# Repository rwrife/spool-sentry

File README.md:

# Spool Sentry

> USB-powered ESP32-C3 monitor for 3D-printing hobbyists to track dry-box humidity, temperature, and filament spool mass through a private local dashboard without controlling heaters or printers.

## Overview

Spool Sentry is a small, repairable monitor for a passive filament dry box. A load cell under one spool records mass trends while a digital temperature/humidity sensor records the box environment. An ESP32-C3-class controller keeps bounded local history and serves a phone/desktop-friendly web interface on the local network. USB CDC remains the setup and recovery path.

The goal is practical awareness: see whether a box is staying dry, record desiccant changes, and estimate remaining filament after the user enters empty-spool mass. It is **not** a dryer controller, printer integration, certified hygrometer, or safety device.

## Motivation

Opaque boxes hide both environmental drift and dwindling material. Stick-on hygrometers show only the present, and manually weighing a spool interrupts storage. Spool Sentry combines two explainable observations without requiring a vendor account, subscription, or internet service.

## Target users

- Home 3D-printing hobbyists who store moisture-sensitive filament
- Small workshops that want a local history for one frequently used spool
- Makers who prefer editable hardware, replaceable sensors, and portable data

## Concrete use cases

- Check current box humidity and temperature from a phone on the same LAN.
- View hourly trends and annotate a desiccant recharge or spool swap.
- Tare/calibrate the scale, enter an empty-spool mass, and see gross/net mass with an uncertainty indicator.
- Export measurements and events as CSV/JSON before clearing local history.
- Recover configuration over USB if Wi-Fi credentials change.

## Intended workflow

1. Assemble the low-voltage carrier, sensor lead, load-cell platform, and enclosure using the bring-up guide that the backlog will create.
2. Power it from a suitable USB 5 V supply; no battery or mains wiring is part of the project.
3. Hold the physical setup button to open a short-lived onboarding session, then configure local Wi-Fi from the device-hosted page or USB CDC.
4. Calibrate with a documented reference mass, enter the spool's empty mass, and place the spool on the platform.
5. Review live values and local trends, add spool/desiccant events, and export or delete data at any time.

## MVP features

- One replaceable load-cell/ADC channel and one digital humidity/temperature channel
- Explicit sensor freshness, calibration state, and invalid/out-of-range statuses
- Gross mass, user-derived net filament estimate, and visible uncertainty—not false precision
- Bounded flash history with retention controls and event annotations
- Responsive local web UI with keyboard, screen-reader, reduced-motion, high-contrast, and non-color-only states
- Versioned CSV/JSON export and JSON backup/restore
- USB CDC provisioning, diagnostics, firmware recovery, and Wi-Fi-free snapshot access
- Physical setup/tare button and status indicator

## Non-goals

- Heater, fan, mains, battery-charging, relay, or printer control
- Fire, smoke, flood, food, medical, or life-safety monitoring
- Certified environmental measurement or guaranteed filament condition/print quality
- Automatic material-type diagnosis, purchasing, cloud accounts, remote internet access, or multi-site fleet management
- Multi-spool inventory, RFID, camera, or slicing software integration in the MVP

## Privacy, permissions, and data storage

Spool Sentry has no cloud backend, telemetry, advertising, or required account. Measurements, calibration data, annotations, and network configuration remain on the device; exports are created only when requested. The local web app requests no phone contacts, location, camera, microphone, Bluetooth, or notification permission. Wi-Fi access is limited to local setup and local device use. USB works without network access.

The baseline LAN protocol is not a promise of hostile-network security: deployment assumes a trusted home/workshop LAN, uses proof-of-presence onboarding, rejects cross-origin mutation, and keeps remote access disabled. Documentation will explain credential reset, export redaction, retention, deletion, and the limitations of unencrypted local HTTP if that remains the chosen transport.

## Safety limits

- SELV USB 5 V input only; use a suitable enclosed/certified USB supply.
- No connection to printer power, heaters, mains, batteries, or safety interlocks.
- Keep electronics away from hot zones, moving printer parts, liquids, and loose filament paths.
- Load readings are informational. Do not use the platform to support people, hazardous loads, or critical processes.
- Humidity/temperature readings and remaining-filament estimates can drift or fail. The device must surface stale/invalid data rather than imply safety or guaranteed print success.

## Hardware and source-of-truth plan

The planned editable KiCad project is:

- `hardware/spool-sentry.kicad_pro`
- `hardware/spool-sentry.kicad_sch`
- `hardware/spool-sentry.kicad_pcb`

These files **do not exist yet**; this repository is currently a documentation/backlog scaffold. The backlog requires real editable KiCad sources, ERC/DRC evidence, firmware/app builds, bring-up measurements, and fabrication outputs before any hardware-complete claim.

Final BOM data belongs in KiCad schematic symbol properties (`Manufacturer`, `MPN`, supplier fields, and notes) and is exported to tracked `bom/bom.csv`. `bom/preliminary-bom.csv` is planning-only and contains no validated sourcing or prices.

## Current status and milestones

**Status: requirements/architecture baseline plus toolchain proof.** The v0.1 requirements, editable architecture diagrams, protocol schema/fixture, risk register, and verification matrix are frozen. A pinned Rust host-test and ESP32-C3 target-link proof exists, but there is still no schematic, PCB, functional firmware/app, calibrated instrument, fabricated board, assembly, ERC/DRC result, flash/boot evidence, or bench/field test.

1. Freeze measurable requirements and risk boundaries.
2. Select exact components from manufacturer datasheets and create the KiCad schematic/BOM.
3. Lay out and verify the carrier PCB.
4. Build firmware and the local web companion against simulated interfaces.
5. Assemble, calibrate, integrate, and publish honest fabrication/release evidence.

See [PLAN.md](PLAN.md), the canonical [v0.1 requirements](docs/requirements.md), [architecture](docs/architecture.md), [risk register](docs/risk-register.md), [verification matrix](docs/verification-matrix.md), and the GitHub issue backlog.

## Development quickstart

The currently implemented checks require Python 3 plus rustup. The proof pins and installs its exact Rust version, components, and ESP32-C3 target:

```sh
./scripts/verify.sh
```

This checks requirement traceability, local Markdown links, the protocol schema/fixture, Rust formatting/clippy/host tests, and an ESP32-C3 release link. See [the toolchain decision](docs/toolchain.md) for exact evidence limits. KiCad 9+, the companion Node/pnpm workspace, selected-part drivers, flashing, and bench procedures arrive in later issues and must not be presented as working yet.

## License

Initial documentation is available under the MIT License. A mature release will add explicit hardware/firmware/software license files and third-party notices before publishing fabrication outputs.

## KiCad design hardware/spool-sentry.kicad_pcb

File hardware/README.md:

# Hardware design artifacts

This directory now carries the schematic source-of-truth for the Spool Sentry carrier board.

## Included files

- `spool-sentry.kicad_pro` / `spool-sentry.kicad_sch`: KiCad 9 project + schematic
- `sym-lib-table`, `fp-lib-table`: local library bindings used by this schematic
- `lib/spool-sentry.kicad_sym`: project-local custom symbols (XIAO ESP32-C3 module, NAU7802 ADC)
- `lib/spool-sentry.pretty/XIAO_ESP32C3.kicad_mod`: project-local XIAO module footprint
- `lib/spool-sentry.dcm`: symbol documentation metadata

## What this schematic covers

- USB 5V SELV power entry and protection path (USB-C UFP + PPTC + TVS + reverse-current block)
- Controller module (`U1`: Seeed XIAO ESP32-C3)
- Bridge ADC path (`U2`: NAU7802) and load-cell connector (`J2`)
- Environmental sensor path (`U3`: SHT40) on shared I2C
- Dedicated user button (`SW1`) for tare/calibration/recovery interactions
- Status RGB indicator (`D3` + current-limit resistors)
- Test points for safe bring-up/diagnostics

## Regenerating verification artifacts

From the repository root:

```bash
# Schematic ERC (text report)
kicad-cli sch erc --format report \
  --output docs/verification/kicad-erc.rpt \
  hardware/spool-sentry.kicad_sch

# Netlist + BOM exports from schematic symbol properties
./scripts/export_schematic_bom.py hardware/spool-sentry.kicad_sch

# Optional external schematic analyzer outputs (JSON + text)
# (path depends on local Hermes skill checkout)
# python3 <path-to-analyze_schematic.py> hardware/spool-sentry.kicad_sch --output docs/verification/schematic-analysis.json
# python3 <path-to-analyze_schematic.py> hardware/spool-sentry.kicad_sch --output docs/verification/schematic-analysis.txt --text
```

The issue-specific validation summary is in
`docs/verification/issue-2-hardware-schematic.md`.

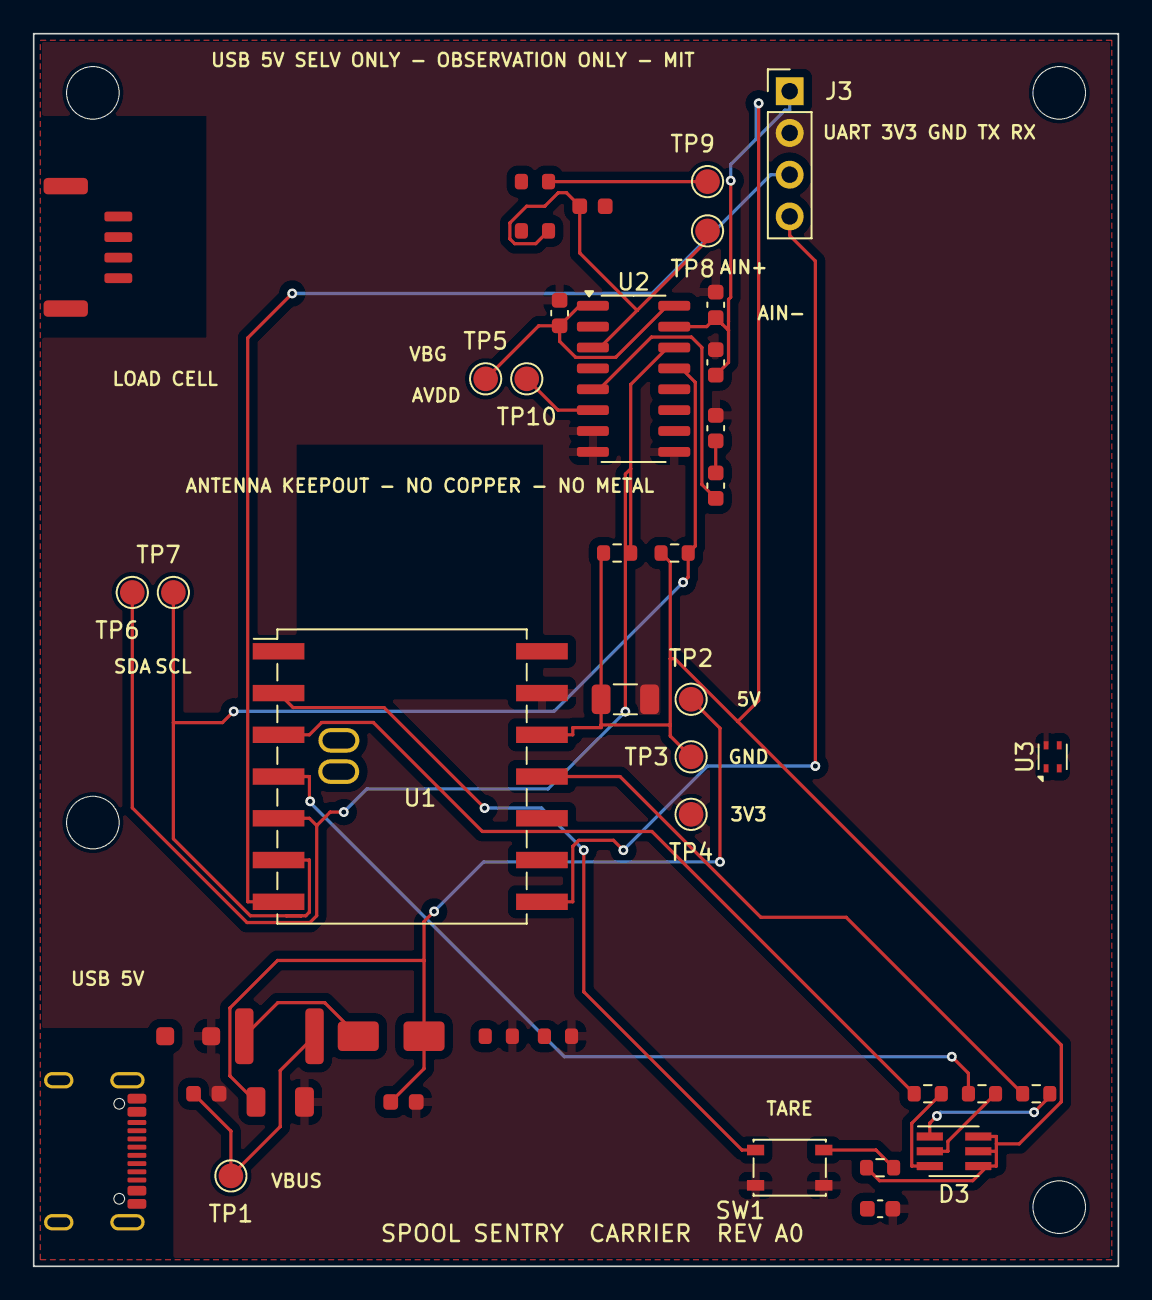
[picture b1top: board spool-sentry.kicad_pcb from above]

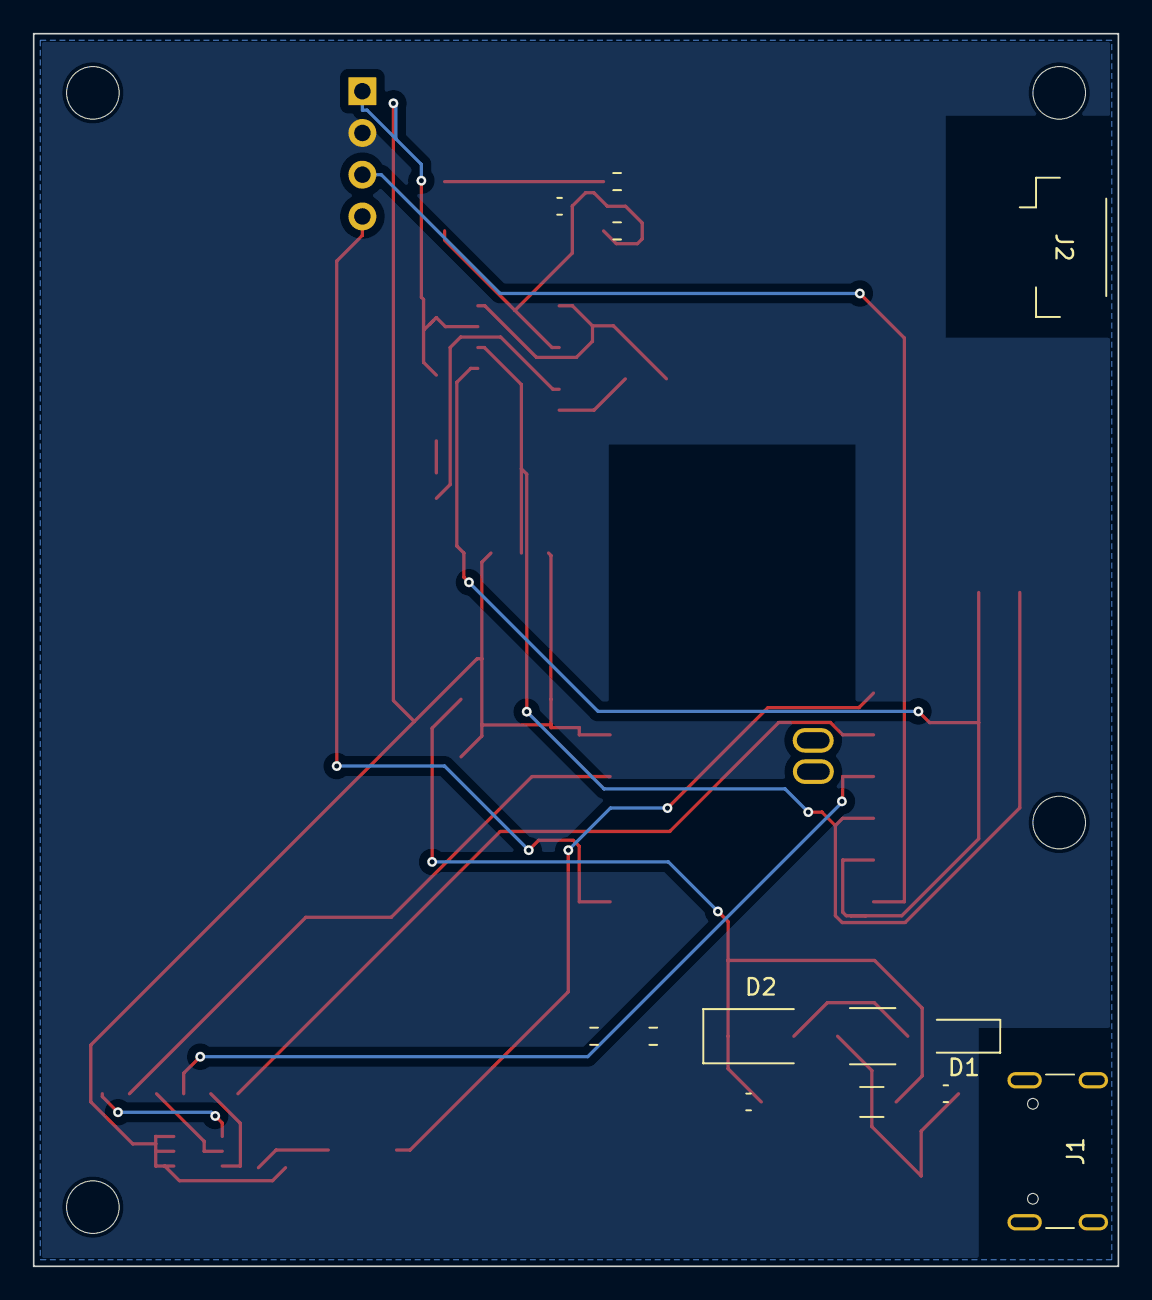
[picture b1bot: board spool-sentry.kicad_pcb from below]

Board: 2 copper layers, 66.0 x 75.0 mm, 46 parts (13 on the bottom side), 25 nets.

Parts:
C1, C3: C_1206_3216Metric
C2, C4, C5, C6, C7, C8, C9, C10, C11: C_0603_1608Metric
D1: D_SOD-123F
D2: D_SMA
D3: LED_Avago_PLCC6_3x2.8mm
F1: Fuse_1812_4532Metric
J1: USB_C_Receptacle_GCT_USB4105-xx-A_16P_TopMnt_Hori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; USB_C_Receptacle_GCT_USB4105-xx-A_16P_TopMnt_Horizontal
J2: JST_GH_SM04B-GHS-TB_1x04-1MP_P1.25mm_Horizontal
J3: PinHeader_1x04_P2.54mm_Vertical
MH1, MH2, MH3, MH4: MountingHole_3.2mm_M3
R1, R2, R3, R4, R5, R6, R7, R8, R9, R10: R_0603_1608Metric
SW1: SW_SPST_PTS810
TP1, TP2, TP3, TP4, TP5, TP6, TP7, TP8, TP9, TP10: TestPoint_Pad_D1.5mm
U1: Seeed XIAO ESP32-C3; XIAO_ESP32C3
U2: SOIC-16_3.9x9.9mm_P1.27mm
U3: Sensirion_DFN-4_1.5x1.5mm_P0.8mm_SHT4x_NoCentralP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; Sensirion_DFN-4_1.5x1.5mm_P0.8mm_SHT4x_NoCentralPad

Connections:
+3V3: C3.1, C4.1, C5.1, D3.4, D3.5, D3.6, J3.1, R5.1, R6.1, R7.1, TP3.1, U1.12, U2.15, U3.3
+5V_XIAO: C1.1, C2.1, D2.1, TP2.1, U1.14
AIN+: C8.1, R3.2, TP8.1, U2.3
AIN-: C8.2, R4.2, TP9.1, U2.2
AVDD_3V0: C6.1, J2.1, TP5.1, U2.1, U2.16
BUTTON_N: C10.1, R7.2, SW1.1, U1.2
CC1: J1.A5, R1.1
CC2: J1.B5, R2.1
GND: C1.2, C2.2, C3.2, C4.2, C5.2, C6.2, C7.2, C10.2, C11.2, D1.2, J1.A1, J1.A12, J1.B1, J1.B12, J1.S1, J2.2, J2.MP, J3.2, R1.2, R2.2, SW1.2, TP4.1, U1.13, U2.7, U2.8, U2.9, U3.4
I2C_SCL: R6.2, TP7.1, U1.6, U2.13, U3.2
I2C_SDA: R5.2, TP6.1, U1.5, U2.14, U3.1
LC_S+: J2.3, R3.1
LC_S-: J2.4, R4.1
LED_B_GPIO: R10.1, U1.11
LED_B_K: D3.1, R10.2
LED_G_GPIO: R9.1, U1.4
LED_G_K: D3.2, R9.2
LED_R_GPIO: R8.1, U1.3
LED_R_K: D3.3, R8.2
PGA_CFILTER: C9.1, U2.5
UART_RX: J3.4, U1.8
UART_TX: J3.3, U1.7
VBG: C7.1, C9.2, TP10.1, U2.6
VBUS: C11.1, D1.1, F1.1, J1.A4, J1.A9, J1.B4, J1.B9, TP1.1
VBUS_FUSED: D2.2, F1.2

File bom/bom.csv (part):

References,Qty,Value,Manufacturer,MPN,Footprint,Datasheet,Supplier,Supplier PN,Estimated Unit Cost USD,Price Observed UTC,Stock Observed,Lifecycle Status,Lifecycle/Availability Evidence UTC,Alternate MPN / Source,Cost Basis,BOM Comments
C1,1,4.7uF 10V X5R,Murata,GRM31CR61A475KA01L,Capacitor_SMD:C_1206_3216Metric,https://www.murata.com/en-global/products/capacitor/mlcc/ove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,DigiKey,490-3902-1-ND,0.20,2026-08-21,Not verified — distributor API credentials unavailable,Lifecycle not machine-verified; check manufacturer PCN/EOL sources before release,2026-08-21,,Public distributor listing/search estimate; not a quote,Protected 5 V bulk capacitor; total carrier input capacitance remains below 10 uF nominal.
"C2, C4, C10",3,100nF 50V X7R,Murata,GRM188R71H104KA93D,Capacitor_SMD:C_0603_1608Metric,https://search.murata.co.jp/Ceramy/image/img/A01X/G101/ENG/G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,DigiKey,490-1519-1-ND,0.02,2026-08-21,Not verified — distributor API credentials unavailable,Lifecycle not machine-verified; check manufacturer PCN/EOL sources before release,2026-08-21,,Public distributor listing/search estimate; not a quote,High-frequency bypass on protected 5 V rail.; High-frequency bypass on the 3V3 rail.; Button hardware debounce; firmware still applies bounded debounce and long-press timing.
C3,1,10uF 10V X5R,Murata,GRM31CR61A106KA01L,Capacitor_SMD:C_1206_3216Metric,https://search.murata.co.jp/Ceramy/image/img/A01X/G101/ENG/G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,LCSC,C97949,0.3351,2026-08-21,22,Lifecycle not machine-verified; check manufacturer PCN/EOL sources before release,2026-08-21,,1 @ $0.3351,Local bulk capacitor on the XIAO 3V3 output; regulator is on the module.
"C5, C6",2,1uF 16V X7R,Murata,GRM188R71C105KA12D,Capacitor_SMD:C_0603_1608Metric,https://www.murata.com/en-global/products/capacitor/mlcc/ove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,DigiKey,TBD—verify before order,0.08,2026-08-21,Not verified — distributor API credentials unavailable,Lifecycle not machine-verified; check manufacturer PCN/EOL sources before release,2026-08-21,,Public distributor listing/search estimate; not a quote,"DVDD local bypass; Nuvoton Rev. 2.6 p.24.; AVDD/LDO local bypass; low-ESR, Nuvoton Rev. 2.6 pp.6,24."
"C7, C8",2,100nF 50V X7R,Murata,GRM188R71H104KA93D,Capacitor_SMD:C_0603_1608Metric,https://www.murata.com/en-global/products/capacitor/mlcc/ove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,DigiKey,TBD—verify before order,0.02,2026-08-21,Not verified — distributor API credentials unavailable,Lifecycle not machine-verified; check manufacturer PCN/EOL sources before release,2026-08-21,,Public distributor listing/search estimate; not a quote,VBG bypass per Nuvoton Rev. 2.6 p.24.; Differential bridge-input filter after the two 47 Ω series resistors.
C9,1,330pF 50V C0G,Murata,GRM1885C1H331JA01D,Capacitor_SMD:C_0603_1608Metric,https://www.murata.com/en-global/products/capacitor/mlcc/ove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,DigiKey,TBD—verify before order,0.05,2026-08-21,Not verified — distributor API credentials unavailable,Lifecycle not machine-verified; check manufacturer PCN/EOL sources before release,2026-08-21,,Public distributor listing/search estimate; not a quote,Optional PGA-output Cfilter between VIN2P and VBG; enable PGA_CAP_EN; Nuvoton p.24.
C11,1,1uF 16V X7R,Murata,GRM188R71C105KA12D,Capacitor_SMD:C_0603_1608Metric,https://www.murata.com/en-global/products/capacitor/mlcc/ove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,DigiKey,490-3897-1-ND,0.08,2026-08-21,Not verified — distributor API credentials unavailable,Lifecycle not machine-verified; check manufacturer PCN/EOL sources before release,2026-08-21,,Public distributor listing/search estimate; not a quote,Local VBUS input bypass; total nominal input capacitance remains below 10 uF.
D1,1,SMF5.0A,Littelfuse,SMF5.0A,Diode_SMD:D_SOD-123F,https://www.littelfuse.com/assetdocs/tvs-diodes-smf-datashee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,DigiKey,F8583CT-ND,0.30,2026-08-21,Not verified — distributor API credentials unavailable,Lifecycle not machine-verified; check manufacturer PCN/EOL sources before release,2026-08-21,,Public distributor listing/search estimate; not a quote,VBUS transient clamp; place at J1 with short return to ground.
D2,1,B140-13-F,Diodes Incorporated,B140-13-F,Diode_SMD:D_SMA,https://www.diodes.com/assets/Datasheets/ds13002.pdf,LCSC,C15759,0.0856,2026-08-21,59660,Lifecycle not machine-verified; check manufacturer PCN/EOL sources before release,2026-08-21,,5 @ $0.0856 each,Series reverse-current block prevents carrier USB input from being back-fed by U1 USB.
D3,1,RGB STATUS,Broadcom Limited,ASMT-YTC7-0AA02,LED_SMD:LED_Avago_PLCC6_3x2.8mm,https://docs.broadcom.com/docs/AV02-3819EN,JLCPCB,C5555828,1.7772,2026-08-22,79,Lifecycle not machine-verified; check manufacturer PCN/EOL sources before release,2026-08-22,,1 @ $1.7772; JLCPCB extended part,"Current YTC7 replacement for obsolete YTC2. Datasheet lead map: 1 KB, 2 KG, 3 KR, 4 AR, 5 AG, 6 AB. Independently driven active-low cathodes; text/icon fault detail remains in the PWA."
F1,1,500mA hold,Bourns,MF-MSMF050-2,Fuse:Fuse_1812_4532Metric,https://www.bourns.com/docs/product-datasheets/mf-msmf.pdf,LCSC,C17313,0.0668,2026-08-21,47400,Lifecycle not machine-verified; check manufacturer PCN/EOL sources before release,2026-08-21,,10 @ $0.0668 each,500 mA hold / 1 A trip PPTC; preserves <500 mA normal-current design target.
J1,1,USB-C POWER ONLY,Global Connector Technology,USB4105-GF-A,Connector_USB:USB_C_Receptacle_GCT_USB4105-xx-A_16P_TopMnt_Horizontal,https://gct.co/files/drawings/usb4105.pdf,LCSC,C3020560,1.0659,2026-08-21,926,Lifecycle not machine-verified; check manufacturer PCN/EOL sources before release,2026-08-21,,1 @ $1.0659,Power-only UFP. CC1/CC2 each use 5.1k Rd. D+/D-/SBU are intentionally NC. Shell to GND.
J2,1,LOAD CELL E+/E-/S+/S-,JST,SM04B-GHS-TB(LF)(SN),Connector_JST:JST_GH_SM04B-GHS-TB_1x04-1MP_P1.25mm_Horizontal,https://www.jst-mfg.com/product/pdf/eng/eGH.pdf,LCSC,C189895,1.1182,2026-08-21,0,Lifecycle not machine-verified; check manufacturer PCN/EOL sources before release,2026-08-21,,1 @ $1.1182; out of stock,"Keyed carrier connector. Pin 1 E+, 2 E-, 3 S+ (green), 4 S- (white). LCSC C189895 was out of stock when checked; verify DigiKey/alternate stock before ordering. Mating housing and contacts are external BOM items."
J3,1,UART DEBUG 3V3,Samtec,TSW-104-07-G-S,Connector_PinHeader_2.54mm:PinHeader_1x04_P2.54mm_Vertical,https://suddendocs.samtec.com/prints/tsw-1xx-xx-xxx-x-xx-xx-mkt.pdf,JLCPCB,C3335156,0.6472,2026-08-21,337,Lifecycle not machine-verified; check manufacturer PCN/EOL sources before release,2026-08-21,,1 @ $0.6472,"Optional 3.3 V UART header: pin 1 3V3, 2 GND, 3 TX (D6/GPIO21), 4 RX (D7/GPIO20). Do not apply 5 V logic."
"R1, R2",2,5.1k 1%,Yageo,RC0603FR-075K1L,Resistor_SMD:R_0603_1608Metric,https://www.yageo.com/upload/media/product/productsearch/dat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,DigiKey,311-5.10KHRCT-ND,0.02,2026-08-21,Not verified — distributor API credentials unavailable,Lifecycle not machine-verified; check manufacturer PCN/EOL sources before release,2026-08-21,,Public distributor listing/search estimate; not a quote,USB-C CC1 Rd; 5.1 kΩ to GND per USB Type-C sink power role.; USB-C CC2 Rd; 5.1 kΩ to GND per USB Type-C sink power role.
"R3, R4",2,47R 1%,Yageo,RC0603FR-0747RL,Resistor_SMD:R_0603_1608Metric,https://www.yageo.com/upload/media/product/productsearch/dat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,DigiKey,311-47.0HRCT-ND,0.02,2026-08-21,Not verified — distributor API credentials unavailable,Lifecycle not machine-verified; check manufacturer PCN/EOL sources before release,2026-08-21,,Public distributor listing/search estimate; not a quote,Bridge input series filter resistor per Nuvoton Rev. 2.6 p.24.
"R5, R6",2,4.7k 1%,Yageo,RC0603FR-074K7L,Resistor_SMD:R_0603_1608Metric,https://www.yageo.com/upload/media/product/productsearch/dat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,DigiKey,311-4.70KHRCT-ND,0.02,2026-08-21,Not verified — distributor API credentials unavailable,Lifecycle not machine-verified; check manufacturer PCN/EOL sources before release,2026-08-21,,Public distributor listing/search estimate; not a quote,Carrier-owned 3.3 V I2C pull-up; do not parallel strong module pull-ups.
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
